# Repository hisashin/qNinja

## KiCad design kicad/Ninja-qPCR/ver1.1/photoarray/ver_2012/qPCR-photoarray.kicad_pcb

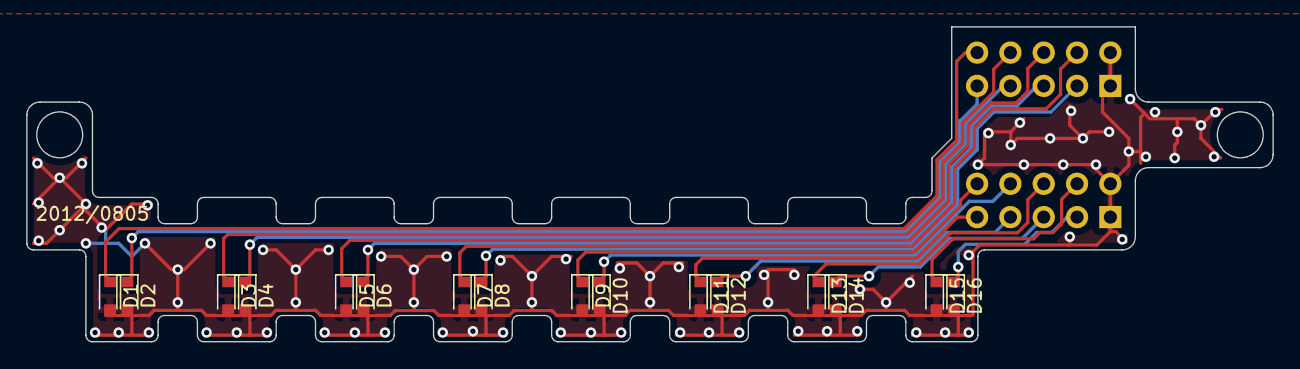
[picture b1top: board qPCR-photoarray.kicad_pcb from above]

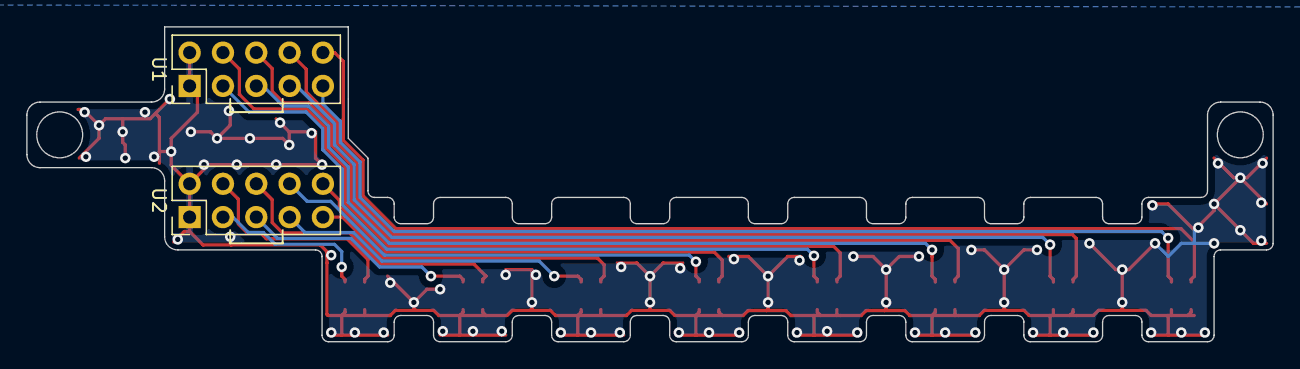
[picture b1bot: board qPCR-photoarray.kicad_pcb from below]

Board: 2 copper layers, 95.0 x 24.0 mm, 18 parts (2 on the bottom side), 17 nets.

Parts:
D1, D2, D3, D4, D5, D6, D7, D8, D9, D10, D11, D12, D13, D14, D15, D16: D_Photo; D_0805
U1, U2: Conn_02x05; Pin_Header_Straight_2x05_Pitch2.54mm

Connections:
GND: D1.2, D2.2, D3.2, D4.2, D5.2, D6.2, D7.2, D8.2, D9.2, D10.2, D11.2, D12.2, D13.2, D14.2, D15.2, D16.2, U1.1, U1.2, U2.1, U2.2
OUT1: D1.1, U1.10
OUT2: D2.1, U1.9
OUT3: D3.1, U1.8
OUT4: D4.1, U1.7
OUT5: D5.1, U1.6
OUT6: D6.1, U1.5
OUT7: D7.1, U1.4
OUT8: D8.1, U1.3
OUT9: D9.1, U2.10
OUT10: D10.1, U2.8
OUT11: D11.1, U2.9
OUT12: D12.1, U2.7
OUT13: D13.1, U2.6
OUT14: D14.1, U2.5
OUT15: D15.1, U2.4
OUT16: D16.1, U2.3

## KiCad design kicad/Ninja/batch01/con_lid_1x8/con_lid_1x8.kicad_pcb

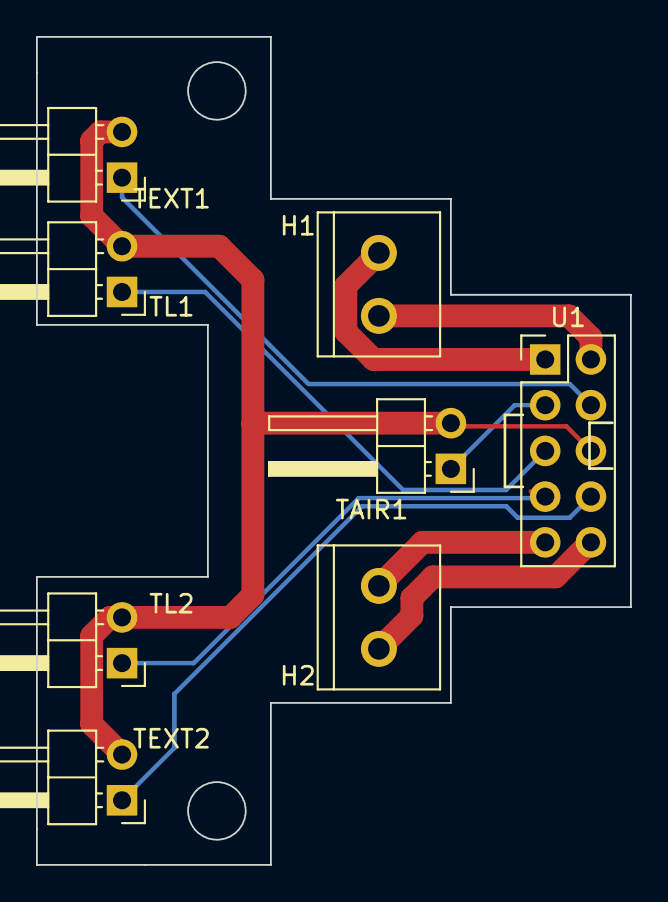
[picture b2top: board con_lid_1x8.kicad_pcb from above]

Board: 2 copper layers, 33.0 x 46.0 mm, 8 parts (0 on the bottom side), 10 nets.

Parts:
H1, H2: Screw_Terminal_01x02; TB_SeeedOPL_320110028
TAIR1: Conn_01x02_Male; Pin_Header_Angled_1x02_Pitch2.54mm
TEXT1, TEXT2: Conn_01x02_Male; Pin_Header_Angled_1x02_Pitch2.54mm
TL1, TL2: Conn_01x02_Male; Pin_Header_Angled_1x02_Pitch2.54mm
U1: Conn_02x05; Pin_Header_Straight_2x05_Pitch2.54mm

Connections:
GND: TAIR1.2, TEXT1.2, TL1.2, TL2.2, U1.6
HEATER1A: H1.1, U1.1
HEATER1B: H1.2, U1.2
HEATER2A: H2.1, U1.9
HEATER2B: H2.2, U1.10
THERM_AIR: TAIR1.1, U1.3
THERM_EXT1: TEXT1.1, U1.4
THERM_EXT2: TEXT2.1, U1.8
THERM_LID1: TL1.1, U1.5
THERM_LID2: TL2.1, U1.7

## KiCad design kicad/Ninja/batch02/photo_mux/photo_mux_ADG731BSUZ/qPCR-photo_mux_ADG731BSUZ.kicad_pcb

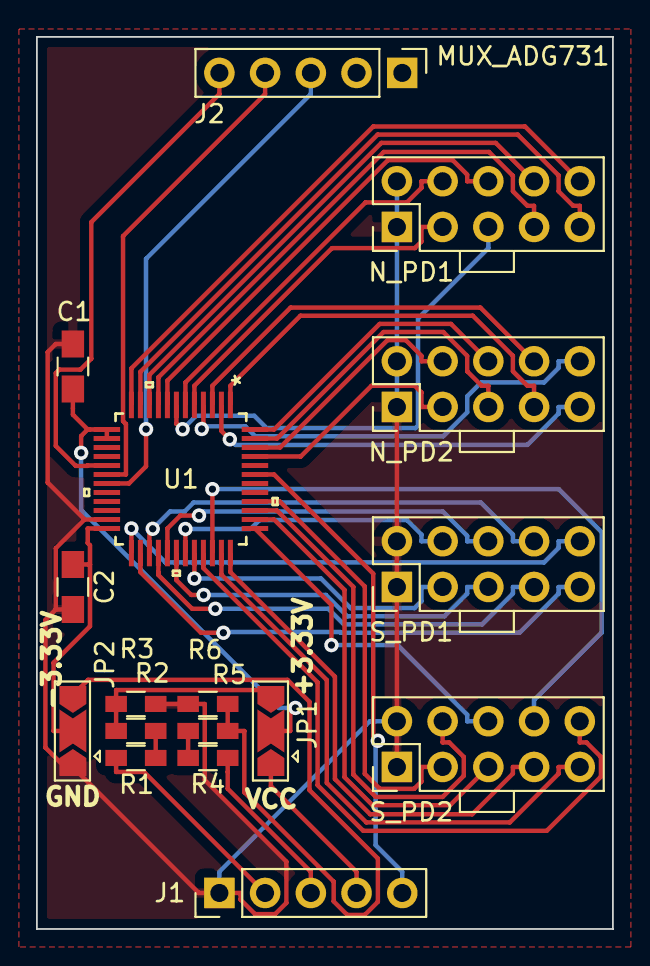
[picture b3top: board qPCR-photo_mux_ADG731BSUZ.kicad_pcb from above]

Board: 2 copper layers, 32.0 x 49.6 mm, 17 parts (0 on the bottom side), 46 nets.

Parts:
C1, C2: C; C_0805_HandSoldering
J1, J2: Conn_01x05_Male; Pin_Header_Straight_1x05_Pitch2.54mm
JP1, JP2: Jumper_3_Open; SolderJumper-3_P2.0mm_Open_TrianglePad1.0x1.5mm
N_PD1, N_PD2: Conn_02x05; Con_2x05
R1, R2, R3, R4, R5, R6: R; R_0603_HandSoldering
S_PD1, S_PD2: Conn_02x05; Con_2x05
U1: ADG731BSUZ

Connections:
+10V: J1.2, R1.1
-10V: J1.3, R4.1
/+3.33V: JP1.3, R2.2, R3.1
/-3.33V: JP2.3, R5.2, R6.1
GND: C1.2, C2.2, J1.1, JP2.1, N_PD1.1, N_PD1.2, N_PD2.1, N_PD2.2, R3.2, R6.2, S_PD1.1, S_PD1.2, S_PD2.1, S_PD2.2, U1.23
N_PD1_OUT1: N_PD1.10, U1.12
N_PD1_OUT2: N_PD1.9, U1.11
N_PD1_OUT3: N_PD1.8, U1.10
N_PD1_OUT4: N_PD1.7, U1.9
N_PD1_OUT5: N_PD1.6, U1.8
N_PD1_OUT6: N_PD1.5, U1.7
N_PD1_OUT7: N_PD1.4, U1.6
N_PD1_OUT8: N_PD1.3, U1.5
N_PD1_OUT9: N_PD2.10, U1.4
N_PD1_OUT10: N_PD2.8, U1.3
N_PD1_OUT11: N_PD2.9, U1.2
N_PD1_OUT12: N_PD2.7, U1.1
N_PD1_OUT13: N_PD2.6, U1.48
N_PD1_OUT14: N_PD2.5, U1.47
N_PD1_OUT15: N_PD2.4, U1.46
N_PD1_OUT16: N_PD2.3, U1.45
unnamed: R1.2, R2.1
unnamed: R4.2, R5.1
PD_MUX_OUT: J1.5, U1.43
PD_MUX_SPI_MOSI: J2.4, U1.18
PD_MUX_SPL_SCLK: J2.3, U1.19
PD_MUX_SYNC: J2.5, U1.17
S_PD1_OUT1: S_PD1.10, U1.25
S_PD1_OUT2: S_PD1.9, U1.26
S_PD1_OUT3: S_PD1.8, U1.27
S_PD1_OUT4: S_PD1.7, U1.28
S_PD1_OUT5: S_PD1.6, U1.29
S_PD1_OUT6: S_PD1.5, U1.30
S_PD1_OUT7: S_PD1.4, U1.31
S_PD1_OUT8: S_PD1.3, U1.32
S_PD1_OUT9: S_PD2.10, U1.33
S_PD1_OUT10: S_PD2.8, U1.34
S_PD1_OUT11: S_PD2.9, U1.35
S_PD1_OUT12: S_PD2.7, U1.36
S_PD1_OUT13: S_PD2.6, U1.37
S_PD1_OUT14: S_PD2.5, U1.38
S_PD1_OUT15: S_PD2.4, U1.39
S_PD1_OUT16: S_PD2.3, U1.40
VCC_LOGIC: J1.4, JP1.1
VDD: C1.1, JP1.2, U1.13, U1.14
VSS: C2.1, JP2.2, U1.24

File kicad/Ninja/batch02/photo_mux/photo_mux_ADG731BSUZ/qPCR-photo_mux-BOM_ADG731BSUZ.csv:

"Id";"Designator";"Package";"Quantity";"Designation";"Supplier and ref";
1;"C1,C2";"C_0805_HandSoldering";2;"C";;;
2;"J1,J2";"Pin_Header_Straight_1x05_Pitch2.54mm";2;"Conn_01x05_Male";;;
3;"JP1,JP2";"SolderJumper-3_P2.0mm_Open_TrianglePad1.0x1.5mm";2;"Jumper_3_Open";;;
4;"N_PD1,N_PD2,S_PD1,S_PD2";"Con_2x05";4;"Conn_02x05";;;
5;"R1,R2,R3,R4,R5,R6";"R_0603_HandSoldering";6;"R";;;
6;"U1";"ADG731BSUZ";1;"ADG731BSUZ";;;

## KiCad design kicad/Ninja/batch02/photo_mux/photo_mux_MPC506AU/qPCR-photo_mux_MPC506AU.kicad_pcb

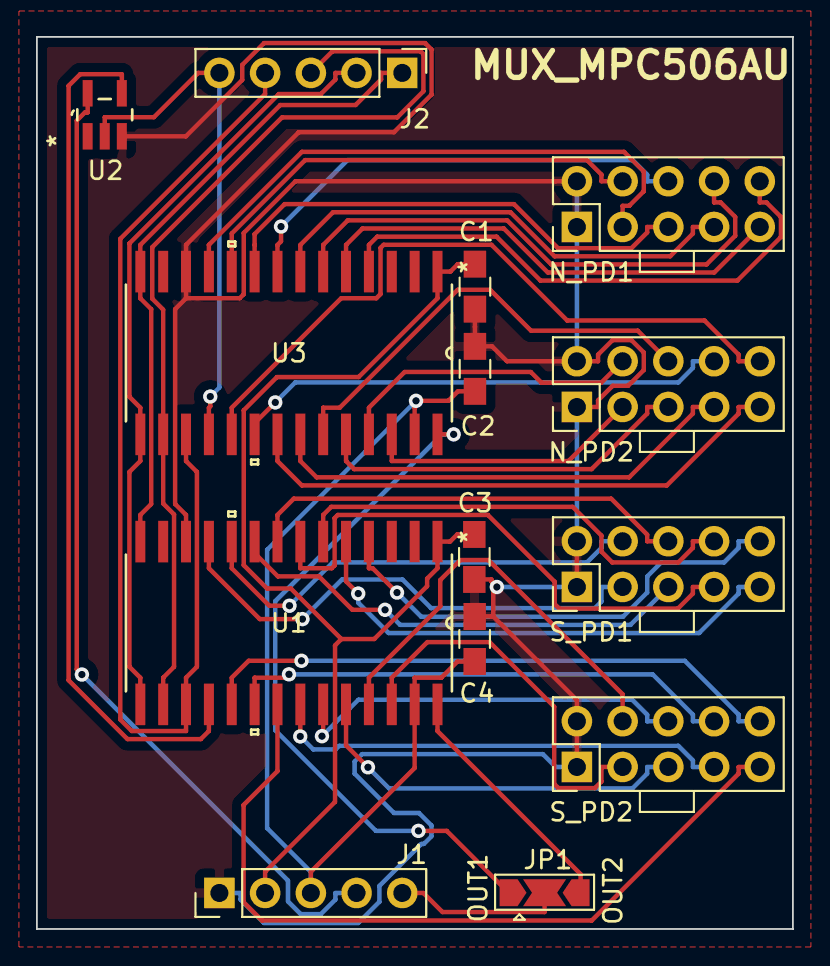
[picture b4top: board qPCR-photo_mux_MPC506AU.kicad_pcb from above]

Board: 2 copper layers, 42.0 x 49.6 mm, 14 parts (0 on the bottom side), 45 nets.

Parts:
C1, C2, C3, C4: C; C_0805_HandSoldering
J1, J2: Conn_01x05_Male; Pin_Header_Straight_1x05_Pitch2.54mm
JP1: Jumper_3_Open; SolderJumper-3_P2.0mm_Open_TrianglePad1.0x1.5mm
N_PD1, N_PD2: Conn_02x05; Con_2x05
S_PD1, S_PD2: Conn_02x05; Con_2x05
U1, U3: MPC506AU
U2: SN74LVC1G04DBVR

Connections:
+10V: C1.1, C3.1, J1.2, U1.1, U3.1
-10V: C2.1, C4.1, J1.3, U1.27, U3.27
/MUX_SELECT_INV: U1.18, U2.4
/PD_MUX_OUT1: JP1.1, U3.28
/PD_MUX_OUT2: JP1.3, U1.28
ADDRESSA0: J2.4, U1.17, U3.17
ADDRESSA1: J2.3, U1.16, U3.16
ADDRESSA2: J2.2, U1.15, U3.15
ADDRESSA3: J2.1, U1.14, U3.14
GND: C1.2, C2.2, C3.2, C4.2, J1.1, N_PD1.1, N_PD1.2, N_PD2.1, N_PD2.2, S_PD1.1, S_PD1.2, S_PD2.1, S_PD2.2, U1.12, U2.3, U3.12
MUX_SELECT: J2.5, U2.2, U3.18
N_PD1_OUT1: N_PD1.10, U3.4
N_PD1_OUT2: N_PD1.9, U3.5
N_PD1_OUT3: N_PD1.8, U3.6
N_PD1_OUT4: N_PD1.7, U3.7
N_PD1_OUT5: N_PD1.6, U3.8
N_PD1_OUT6: N_PD1.5, U3.9
N_PD1_OUT7: N_PD1.4, U3.10
N_PD1_OUT8: N_PD1.3, U3.11
N_PD1_OUT9: N_PD2.10, U3.19
N_PD1_OUT10: N_PD2.8, U3.20
N_PD1_OUT11: N_PD2.9, U3.21
N_PD1_OUT12: N_PD2.7, U3.22
N_PD1_OUT13: N_PD2.6, U3.23
N_PD1_OUT14: N_PD2.5, U3.24
N_PD1_OUT15: N_PD2.4, U3.25
N_PD1_OUT16: N_PD2.3, U3.26
PD_MUX_OUT: J1.5, JP1.2
S_PD1_OUT1: S_PD1.10, U1.4
S_PD1_OUT2: S_PD1.9, U1.5
S_PD1_OUT3: S_PD1.8, U1.6
S_PD1_OUT4: S_PD1.7, U1.7
S_PD1_OUT5: S_PD1.6, U1.8
S_PD1_OUT6: S_PD1.5, U1.9
S_PD1_OUT7: S_PD1.4, U1.10
S_PD1_OUT8: S_PD1.3, U1.11
S_PD1_OUT9: S_PD2.10, U1.19
S_PD1_OUT10: S_PD2.8, U1.20
S_PD1_OUT11: S_PD2.9, U1.21
S_PD1_OUT12: S_PD2.7, U1.22
S_PD1_OUT13: S_PD2.6, U1.23
S_PD1_OUT14: S_PD2.5, U1.24
S_PD1_OUT15: S_PD2.4, U1.25
S_PD1_OUT16: S_PD2.3, U1.26
VCC_LOGIC: J1.4, U2.5

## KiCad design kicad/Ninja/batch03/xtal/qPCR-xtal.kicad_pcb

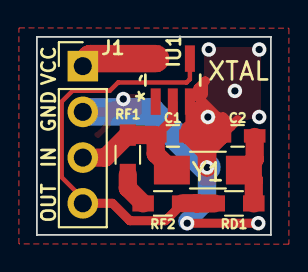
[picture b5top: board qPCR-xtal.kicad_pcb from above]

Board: 2 copper layers, 13.0 x 11.0 mm, 8 parts (0 on the bottom side), 6 nets.

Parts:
C1, C2: 10pF; C_0603_HandSoldering
J1: Conn_01x04_Male; Pin_Header_Straight_1x04_Pitch2.54mm
RD1: 560kOhm; R_0603_HandSoldering
RF1, RF2: 10M; R_0603_HandSoldering
U1: SN74LVC1G04DBVR
Y1: 32.768kHz; C_1206_HandSoldering

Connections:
GND: C1.2, C2.2, J1.2, U1.3
IN: C1.1, J1.3, RF1.2, U1.2, Y1.1
unnamed: C2.1, RD1.2, Y1.2
unnamed: RF1.1, RF2.2
OUT: J1.4, RD1.1, RF2.1, U1.4
VCC: J1.1, U1.5

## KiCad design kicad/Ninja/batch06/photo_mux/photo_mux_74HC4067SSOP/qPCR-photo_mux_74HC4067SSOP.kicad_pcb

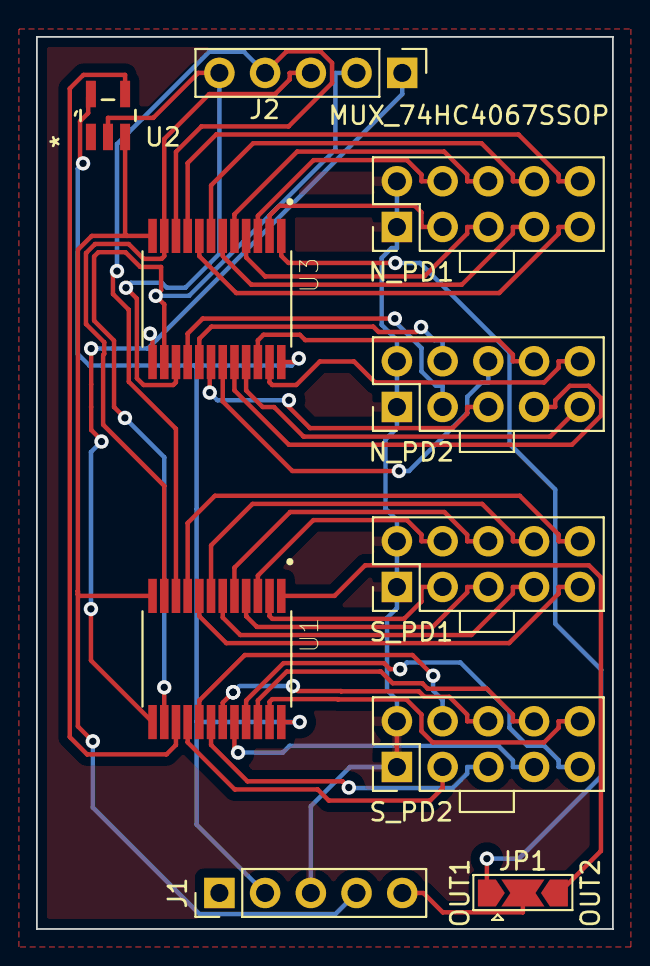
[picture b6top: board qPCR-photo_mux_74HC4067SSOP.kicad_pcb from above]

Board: 2 copper layers, 32.0 x 49.6 mm, 10 parts (0 on the bottom side), 44 nets.

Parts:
J1, J2: Conn_01x05_Male; Pin_Header_Straight_1x05_Pitch2.54mm
JP1: Jumper_3_Open; SolderJumper-3_P2.0mm_Open_TrianglePad1.0x1.5mm
N_PD1, N_PD2: Conn_02x05; Con_2x05
S_PD1, S_PD2: Conn_02x05; Con_2x05
U1, U3: CD74HC4067M96; SOP65P780X200-24N
U2: SN74LVC1G04DBVR

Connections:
-1V: J1.4, U1.12, U2.3, U3.12
/MUX_SELECT_INV: U1.15, U2.4
/PD_MUX_OUT1: JP1.1, U3.1
/PD_MUX_OUT2: JP1.3, U1.1
ADDRESSA0: J2.4, U1.10, U3.10
ADDRESSA1: J2.3, U1.11, U3.11
ADDRESSA2: J2.2, U1.14, U3.14
ADDRESSA3: J2.1, U1.13, U3.13
LOGIC_3V3: J1.2, U1.24, U2.5, U3.24
MUX_SELECT: J2.5, U2.2, U3.15
N_PD1_OUT1: N_PD1.10, U3.9
N_PD1_OUT2: N_PD1.9, U3.8
N_PD1_OUT3: N_PD1.8, U3.7
N_PD1_OUT4: N_PD1.7, U3.6
N_PD1_OUT5: N_PD1.6, U3.5
N_PD1_OUT6: N_PD1.5, U3.4
N_PD1_OUT7: N_PD1.4, U3.3
N_PD1_OUT8: N_PD1.3, U3.2
N_PD1_OUT9: N_PD2.10, U3.23
N_PD1_OUT10: N_PD2.8, U3.22
N_PD1_OUT11: N_PD2.9, U3.21
N_PD1_OUT12: N_PD2.7, U3.20
N_PD1_OUT13: N_PD2.6, U3.19
N_PD1_OUT14: N_PD2.5, U3.18
N_PD1_OUT15: N_PD2.4, U3.17
N_PD1_OUT16: N_PD2.3, U3.16
PD_MUX_OUT: J1.5, JP1.2
PHOTO_GND: J1.3, N_PD1.1, N_PD1.2, N_PD2.1, N_PD2.2, S_PD1.1, S_PD1.2, S_PD2.1, S_PD2.2
S_PD1_OUT1: S_PD1.10, U1.9
S_PD1_OUT2: S_PD1.9, U1.8
S_PD1_OUT3: S_PD1.8, U1.7
S_PD1_OUT4: S_PD1.7, U1.6
S_PD1_OUT5: S_PD1.6, U1.5
S_PD1_OUT6: S_PD1.5, U1.4
S_PD1_OUT7: S_PD1.4, U1.3
S_PD1_OUT8: S_PD1.3, U1.2
S_PD1_OUT9: S_PD2.10, U1.23
S_PD1_OUT10: S_PD2.8, U1.22
S_PD1_OUT11: S_PD2.9, U1.21
S_PD1_OUT12: S_PD2.7, U1.20
S_PD1_OUT13: S_PD2.6, U1.19
S_PD1_OUT14: S_PD2.5, U1.18
S_PD1_OUT15: S_PD2.4, U1.17
S_PD1_OUT16: S_PD2.3, U1.16

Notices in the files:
parts and their libraries:
Copyright 2016 Accelerated Designs. All rights reserved.
